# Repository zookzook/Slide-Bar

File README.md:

# Slide-Bar

Simple board for a slide potentiometer and visible feedback.

The idea behind it: With a slide potentionmeter an analog value can be changed. The change or the value is displayed with a bar display (10 LEDs). The board is designed so that you can connect several to each other. The power supply is thus forwarded from board to board.

You can thus combine the components. If you have three of the sliders, you can use the three analog values for one RGB LED. With the three slide potentionmeter thus a certain color can be adjusted.

Okay, that's a bit boring, but great fun for kids. If you add a chic frame and a nice instrument plate to the whole thing, you get a super game for children who like to fiddle around everywhere. Ultimately, that's the idea: a simple game machine and different input components (sliding and turning meters, switches) and output components (RGB LEDs, bar LEDs) with different effects (animated, cursor, Zini mode).

# How does it work?

The whole thing is controlled by an Attiny85 chip. With the help of two shift registers the LEDs are controlled. A rotary potentiometer controls the mode. There are six modes:

1) Standard slider mode: The value is displayed from bottom to top with the LEDs switched on.
2) Analogous to mode 1. The active LEDs are animated pulsatingly. In the red area, the pulse rate is higher.
3) Cursor mode. The value is displayed as a blinking cursor. If the potentiometer is changed, the flashing will be deactivated during the modification time.
4) Zini mode. When the value changes, the cursor moves, pulling a tail behind it. The previously visited LEDs are slowly faded out.
5) still in the planning stage
6) Dropping mode. A cursor is moving from the current position to the first position of the slider.

The power comes from a USB-A cable. Each two pin headers for 5V + and GND are located on the sides, so that the boards can be placed side by side or one below the other.

# Board preview

You can order pretty boards from here: https://aisler.net/p/UGINGUNY

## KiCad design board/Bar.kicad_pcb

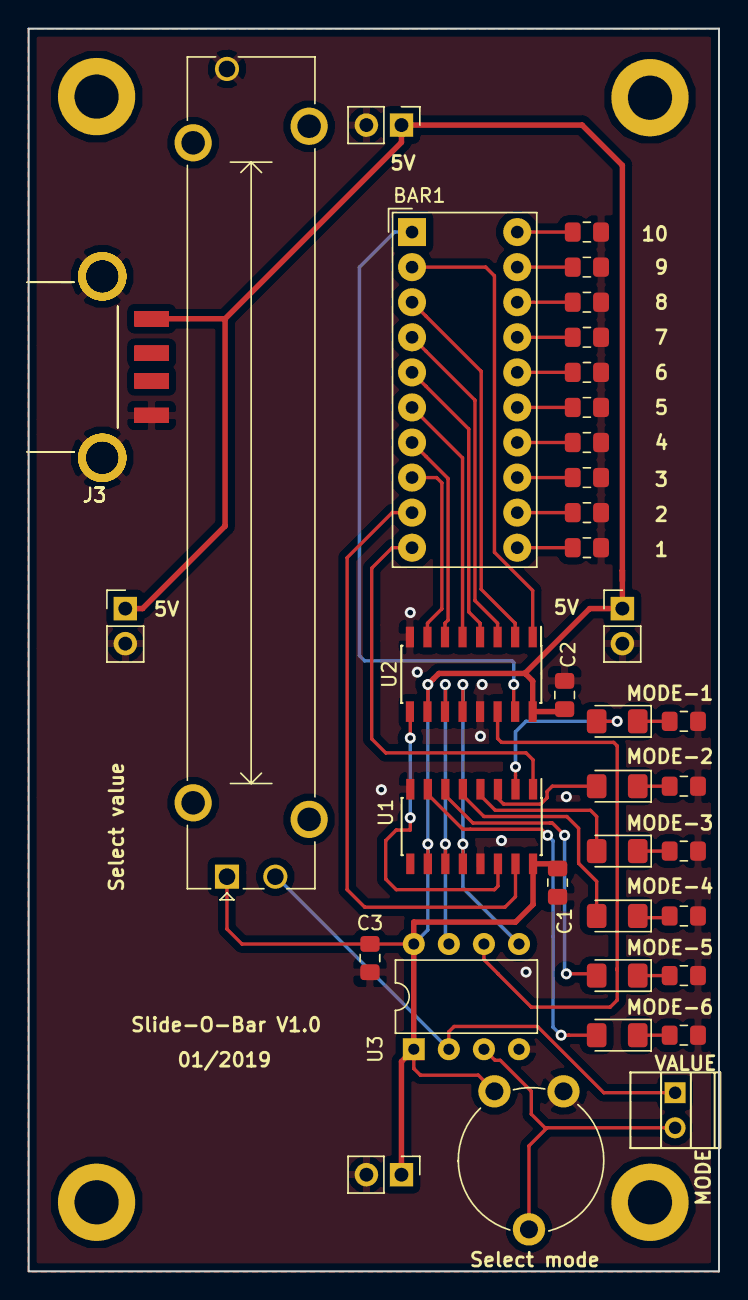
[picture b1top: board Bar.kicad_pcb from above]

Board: 2 copper layers, 50.0 x 90.0 mm, 39 parts (0 on the bottom side), 42 nets.

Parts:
BAR1: DC7G3HWA; HDSP-4850
C1, C2, C3: 100nF; C_0805_2012Metric_Pad1.15x1.40mm_HandSolder
D1, D2, D3, D4, D5, D6: LED; LED_1206_3216Metric_Pad1.42x1.75mm_HandSolder
J1, J2, J5, J6: SUPPLY; PinHeader_1x02_P2.54mm_Vertical
J3, J3#2, J3#3: USB_A; LUM_2410_06_USB_A_SMD
J4: Screw_Terminal_01x02; AKZ692_2_2_54
R1, R2, R3, R4, R5, R6, R7, R8, R9, R10, R11, R12, R13, R14, R15, R16: 100; R_0805_2012Metric_Pad1.15x1.40mm_HandSolder
RV1: R_POT; Potentiometer_Bourns_PTA4543_Single_Slide
RV2: R_POT; Potentiometer_Piher_PT-10-V10_Vertical
U1, U2: 74HC595; SOIC-16_3.9x9.9mm_P1.27mm
U3: ATtiny85-20PU; DIP-8_W7.62mm

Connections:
+5V: C1.1, C2.1, C3.1, J1.1, J2.1, J3.1, J3#2.1, J3#3.1, J5.1, J6.1, RV1.1, RV2.1, U1.10, U1.16, U2.10, U2.16, U3.1, U3.8
/CLOCK: U1.11, U2.11, U3.7
/DATA: U2.14, U3.6
/LATCH: U1.12, U2.12, U3.5
/MODE: J4.2, RV2.2, U3.3
/OUTPUT: J4.1, RV1.2, U3.2
/OUT_1: D1.2, U1.2
/OUT_2: D2.2, U1.3
/OUT_3: D3.2, U1.4
/OUT_4: D4.2, U1.5
/OUT_5: D5.2, U1.6
/OUT_6: D6.2, U1.7
/SEG_1: BAR1.1, U2.15
/SEG_2: BAR1.2, U2.1
/SEG_3: BAR1.3, U2.2
/SEG_4: BAR1.4, U2.3
/SEG_5: BAR1.5, U2.4
/SEG_6: BAR1.6, U2.5
/SEG_7: BAR1.7, U2.6
/SEG_8: BAR1.8, U2.7
/SEG_9: BAR1.9, U1.15
/SEG_10: BAR1.10, U1.1
/SHIFT_OUT: U1.14, U2.9
GND: C1.2, C2.2, C3.2, J1.2, J2.2, J3.4, J3.5, J3#2.4, J3#2.5, J3#3.4, J3#3.5, J5.2, J6.2, R1.2, R2.2, R3.2, R4.2, R5.2, R6.2, R7.2, R8.2, R9.2, R10.2, R11.2, R12.2, R13.2, R14.2, R15.2, R16.2, RV1.3, RV2.3, U1.8, U1.13, U2.8, U2.13, U3.4
unnamed: BAR1.11, R10.1
unnamed: BAR1.12, R9.1
unnamed: BAR1.13, R8.1
unnamed: BAR1.14, R7.1
unnamed: BAR1.15, R6.1
unnamed: BAR1.16, R5.1
unnamed: BAR1.17, R4.1
unnamed: BAR1.18, R3.1
unnamed: BAR1.19, R2.1
unnamed: BAR1.20, R1.1
unnamed: D1.1, R11.1
unnamed: D2.1, R12.1
unnamed: D3.1, R13.1
unnamed: D4.1, R14.1
unnamed: D5.1, R15.1
unnamed: D6.1, R16.1
unnamed: J3.2, J3#2.2, J3#3.2
unnamed: J3.3, J3#2.3, J3#3.3

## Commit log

2019-01-02 added leds for representing the mode added first version of the software
2019-01-03 using spi, added code for different modes, added filter for the analog input
2019-01-03 using A2 for selecting operation mode
2019-01-05 added mode 3 and mode 4
2019-01-14 final board
2019-01-19 Updated schema and board preview
2019-01-19 converted schema pdf to png
2019-01-20 added files for mounting (3d printing)
2019-01-20 clean up code
2019-01-20 added mounting bracket for three boards
2019-01-25 added mode 5 + 6, flipped bar order
2019-02-08 added 3d models
2019-02-08 updated doc
2019-02-10 added aisler.net link
2019-02-10 fixed typo
